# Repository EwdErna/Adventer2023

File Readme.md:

# Blender でキーボードケースのレンダーを作る

これを、  
  
こうします。  

## 目次

星が一つついている項目(★)はキーキャップ関連です。  
星が二つ付いている項目(★★)は基板関連です。  
必要ない場合は飛ばしてかまいません。  
特に、★ を行った場合 ★★ はほぼ見えません。  
見えないところにこだわる~~異常者~~方だけが参照していただければよいかなと思ってます。

- ★ キーボードを作る
  - ★ Keyboard Layout Editor でキー配置を作る
  - ★★ KiCAD で基板データを作る
  - ケースを作る
- Blender 用に出力する
  - ケースの出力
  - ★ キー配置の出力
  - ★★ 基板の出力
- Blender の設定
  - 単位関連の設定
  - レンダリング関連の設定
  - ★ キー配置インポート用の設定
- ケースを配置する
  - インポート
  - 座標設定
  - ★ 面をきれいにする
- マテリアルをいじる
  - アルマイト
  - ヘアライン
  - スモークアクリル
- レンダリング
  - 足場
  - ライティング
  - カメラ
  - レンダリング
- ★ キーキャップを配置する
  - keyboard-layout.json の読み込み
  - サイズ設定
  - 配置
- ★★ 基板を配置する
  - 基板データの読み込み
  - データクリーンアップ
  - 配置

## キーボードを作る

レンダーに使うキーボードの各種データを作成していきます。すでに存在する場合は飛ばしてよいです。

### ★ Keyboard Layout Editor でキー配置を作る

記事冒頭で提示したように、キーボードの配置を考えていきます。  

こちらのサイトで、自分の使いたいキー配置を作成します。  
[Keyboard Layout Editor](http://keyboard-layout-editor.com)  
刻印や色、(一部ですが)プロファイルも反映されるので、こだわる場合は設定しておくとよいです。

詳しい使い方はあちこちのサイトに紹介されているので触れません。

### ★★ KiCAD で基板データを作る

上記の配置を達成する基板データを作成します。  

こちらも詳細は省きます。サリチル酸さんの本を買ってください。 (ダイマ)
https://booth.pm/ja/items/4410329

### ケースを作る

上記のキーボードを収めるケースを作成します。  

特に制約はないですが、自分のデータでは以下のように基板を収める部分(の、bounding box)が原点に対して上下・左右対称になるよう作成しています。  
  
また図にはありませんが、PCB が水平な状態で入る向き(伝わる？)で作るのもおすすめです。  
後々位置合わせが楽になるので意識してみるとよいと思います。

参考文献としてサリチル酸さんの本を買ってください。(ダイマ)  
https://salicylic-acid3.booth.pm/items/4982088

## Blender 用に出力する

作成した各種データを、Blender で読み込める形式で出力します。

### ケースの出力

以下は FreeCAD の場合です。他の CAD を使う方はいい感じに読み替えてください。

パーツを選択した状態で、`ファイル` > `エクスポート`を選択します。  

Blender で読み込める形式ならどれを選んでもよいですが、ここでは`Wavefront OBJ`形式を選択しています。  

Blender で(デフォルトで)読み込める形式は、Blender を開き`File` > `Import`から確認できます。  
  
形式によって扱いずらいデータが出てくる場合もあるので、個人的には OBJ で済ませるのが良いかなと思っています。

### ★ キー配置の出力

KLE にて、以下どちらかの方法で keyboard-layout.json をダウンロードできます(どっちも同じです)。  

### ★★ 基板の出力

以下は KiCAD の場合です。他の EDA を使う方はいい感じに読み替えてください。

`ファイル` > `エクスポート` > `VRML...`を選択します。  
  
VRML を使っている理由としては、

- Blender で直接インポートできる
- 色付き

の二点です。あとでわかる通りめちゃくちゃめんどくさいデータ構造なので、ほかにいいものあれば教えてください。

## Blender の設定

やや個人の好みが入っていますがこの設定しとくとやりやすいよってやつです。

### 単位関連の設定

図の三か所を変更します。  
  
左から順に、

- 単位系のデフォルトを`mm`に
  - キーボードのスケールに合わせる
- カメラのクリッピング距離を変更
  - デフォルトだとちょっと近づくとすぐに見えなくなる
  - 実際の値はよしなに
- グリッドを`mm`単位に
  - デフォルトだと広すぎて扱いづらい(好み)
  - 実際の値はよしなに

### レンダリング関連の設定

好みです。ただし、以下の解説では Cycles を前提にしたマテリアル設定が出てくるため、Eevee では見た目が大きく異なる/使用できない場合があります。  

- `Render Engine`を`Cycles`に
- `Device`を設定
  - Cycles にしない場合は出てこない
  - GPU があるなら GPU Compute に
  - ないなら CPU のままでよいがクソ重い
    - 比較材料として、今回のレンダリング画像の出力には CPU で 3 時間、GPU で 5 分ほどかかりました。

### ★ キー配置インポート用の設定

以下のサイトから Blender のアドオンをダウンロードします。  
  
https://github.com/Kirpal/Keyboard-Layout-Editor-for-Blender/releases/tag/v3.3

ダウンロードした zip を Blender で読み込みます。  

インストールしたアドオンを有効化します。  

## ケースを配置する

ケースデータを読み込み、シーンに配置していきます。

### インポート

`File` > `Import` > `Wavefront(.obj)`を選択します。  
obj 以外で出力した場合は適切に読み替えてください。  

### 座標設定

出力時の設定にもよりますが馬鹿デカいものが出てくると思います。  
その場合はいい感じにサイズを縮小してください。  
画像の場合、`s.001` > `右クリックorEnter`で 1/1000 にすると実際のスケールになります。

原点や向きが扱いづらいのでいい感じにしていきます。  
順に、

- `gz88.888`(数値は CAD 中の原点からケース最下部までの距離)
- `gy88.888`(同様にケース底面までの距離)
- `rx88.888`(同様にケース底面が水平になる角度)

で修正しました。  

### 面をきれいにする

好みです＆とても面倒です。気にならない方はぜひ飛ばしてください。  
個人的にはかなり見た目に影響すると思っているので、できるだけ設定しています。

CAD から読み込んだ OBJ データは下図のように曲面がカクカクに描画されていることがほとんどです。  
  
これを、以下のように滑らかにします。  

#### デフォルト設定でいい感じになるか試す

「滑らかな曲面」と「角ばった辺」で、大きく角度が異なる場合はこの設定のみで事足ります。  
オブジェクトを選択した状態で、`Object` > `Shade Auto Smooth` を選択します。  

「滑らかな曲面」と判定される角度を調節することで、きれいに曲面とエッジが分かれてくれる場合はこれで終了です。  

#### いい感じにならない場合

今回の自分のケースのように、角度の浅い面のつながりがある場合、Auto Smooth だけでは対応しきれません。  

その場合は、「角度が浅いが角の出る辺」をそのようにマークしてあげることで、いい感じになります。

平らな面の一つを選択し、`Select` > `Select Linked` > `Linked Flat Faces`を選択します。  
  
この時画面左下にメニューが出ていますので、調整します。小さく設定することで浅い角度の面でも切り分けてくれるようになりますが、フィレットのような浅い角度でつながっている曲面もぶつ切りになるようになります。  
  
滑らかにつながっていてほしい面はできるだけつながっていて、つながっていてほしくない＝エッジがはっきり出てほしい面は一つもつながっていない状態にします。(後者は後から分けるのが面倒です。前者を妥協して後から直すほうが楽)  
`Select` > `Select Loops` > `Select Boundary Loop`を選択することで、選択された面の外周の辺だけを選択できます。  
  
この状態で、`Ctrl+E` > `Mark Sharp`を選択することで辺を「角の出る辺」としてマークすることができます。  

この操作を繰り返すことで、いい感じにエッジが出るように設定できます。  

## マテリアルをいじる

せっかくレンダリングするのでマテリアルをいい感じにしましょう。  
細かい設定だったり一般論だったりは他のサイトに任せますので、よく使ってるマテリアル設定を貼ります。  
※前述したとおり Cycles 前提のマテリアルです。あと適当なのでそんなにそれっぽくなかったりクソ重かったりします。

### アルマイト

### ヘアライン

### スモークアクリル

## レンダリング

レンダリングに向けて準備をし、実際にレンダリングしていきます。

### 足場

適当です。  
`Add` > `Mesh` > `Cube`を追加し、`s` > `Shift+z` > `2000`で 2m 四方の大きさにしたものを位置調節しました。  
  
マテリアルも適当です。なんか木っぽい感じにしようとしました。  

### ライティング

`Add` > `Light` > `Area Light`からライトを追加します。他のでもいいです。  
三点照明法っぽい感じにしようとしてます。毎度むずいです。誰か助けてくれ  
  
見切れてますが上のほうに一個ライトがあります。

### カメラ

`Add` > `Camera`からカメラを追加します。なんかいい感じに見えるように配置します。誰か助けてくれ  

### レンダリング

`Image` > `Render Image`を押すとレンダリングが始まります。GPU がない人は耐えましょう。  

一旦完成です。  
ここから先はこだわる人向けです。

## ★ キーキャップを配置する

キーボードなのでキーキャップぐらいほしいですよね。  
安心してください、簡単にできますよ。

### keyboard-layout.json の読み込み

最初のほうでダウンロードした json ファイルを Import します。

`File` > `Import` > `KLE Raw Data(.json)`があるので、こちらを選択します。  

ダウンロードした json ファイルを開きます。  

ちょっと時間がかかりますがインポートが始まります。

### サイズ設定

いつも通りでかいのでサイズ調整します。(オレンジのやつがケース)  

選択が外れてしまっている場合、Keyboard というコレクションが追加されているので`右クリック` > `Select Objects`ですべてのパーツを選択できます。  

今回は`s.1`で 1/10 にしました。  

雑なケースがついてきますがいらないので消します。  

スイッチもついてます。なぜかちょっと小さいのでそのまま使うのはお勧めしません。  
使う場合はすべて選択したのち、pivot を Individual Origin にしたうえで、`s1.27`とすると実寸大に近くなります。  

私は後述の設定をしているので基本消してます。

さすがに時間がかかるので今回はやりませんでしたが、普段はさらに、キーキャップのポリゴン数を減らすクリーンアップ作業をしています。

### 配置

配置を楽にするため、すべてのオブジェクトを一つのオブジェクトの子にします。

`Add` > `Empty` > `Plain Axis`から空オブジェクトを作成します。  
  
変なことをしてなければキーキャップ外形の中心に十字架の中心がいるはずです。ずれていたらインポートからやり直したほうが早いです。

キャップ(スイッチを残している人はスイッチも)をすべて選択した後、先ほどの empty を追加選択します(十字架が薄いオレンジ、ほかが濃いオレンジになると思います。色変えてる人は知りません)。  
`Ctrl+p` > `Object`で親子関係を作成します。  
  
親子関係を作ったので、empty を移動させたり回転させればキャップがまとめて移動したり回転したりします。

empty をいい感じにケースの床に移動させます。(ずれてないように見えててもやっといたほうが無難です)  
ケースを選択した状態で、`Object` > `Snap` > `Cursor to Selected`を選択します。カーソル(赤白の点線の丸と黒いひげのやつ)がケース原点に移動します。

Empty を選択した状態で、`Object` > `Snap` > `Selection to Cursor`を選択します。empty 原点がカーソル＝ケース原点に移動します。

あとは、向きや高さを合わせます。先に向きを合わせ(`rx7`：グローバルの x 軸で回転)、その後高さを合わせる(`gzz12`：ローカルの z 軸で移動)と楽です。  

これで完成です。  

ここから先は見えないところに時間をかけてこだわる~~狂人~~僕みたいな人向けの内容になります。

## ★★ 基板を配置する

基板のデータを読み込み、キーキャップの下に仕込みます。  
プレート等も同様の手順で作成できるので応用してみてください(svg あるならそっちのほうが楽です)。

### 基板データの読み込み

先にコレクションを作り、選択しておくと楽です。(キーキャップの項で説明した Select Objects がほぼ必須)  
`File`>`Import`>`X3D Extensible 3D(.x3d/.wrl)`から KiCAD が吐いた wrl ファイルを読み込みます。  

### データクリーンアップ

毎度のことながらクソでかいので縮めます。 ... の前に、まずはデータをまとめます。  
Hierarcy を見るとわかる通り非常にオブジェクトが多いです。何かというと、キースイッチの各面がなぜかバラバラに出てきています。(SHAPE_1 ～ SHAPE_160 くらいまでがキースイッチのポリゴン)  
そのままでは扱えたものではないので、一つのオブジェクトにまとめてしまいます。

hierarchy を一番下までスクロールし(この時選択解除しないように気を付けてください)、下から何個目かにある、マテリアルが緑色のオブジェクトを`Ctrl+Click`で選択してください。  
基板の面面か裏面で、原点が基板中央になっています(なっていなかったら、そうなっている別のオブジェクトを使ってください)。  

`Ctrl+j`で一つのオブジェクトにまとめ、その後 pivot を Cursor にした状態で縮小(`s.001`)します。

まとめただけで面がばらばらだとライティング時に不都合なので、くっつけられる場所はくっつけていきます。  
編集モードに入り、選択を全解除します。その後、以下の手順をすべてのマテリアルに対して繰り返します。  

- マテリアルを一つ選択し、`Select`で対応する面を選択します。
- `Mesh` > `Clean Up`(u キー) >`Merge by distance`(b キー)を選択します。
- (初回のみ)Merge Distance を 0.01mm とかそこらにします(細かい部品がつぶれるのを防ぐため。よしなに)。
- 何もないところをクリックし、選択解除します。

すべてのマテリアルについてマージしたらクリーンアップ完了です。

キーキャップ同様今回はスキップしましたが、普段は各部品の Smooth 設定をやってます。バカじゃないの？

### 配置

オブジェクトモードに戻り、キーキャップの時と同様`Object`>`snap`を活用して原点に位置合わせします。  

回転、座標合わせをして完成です。  

最終的なレンダリング結果はこちら。

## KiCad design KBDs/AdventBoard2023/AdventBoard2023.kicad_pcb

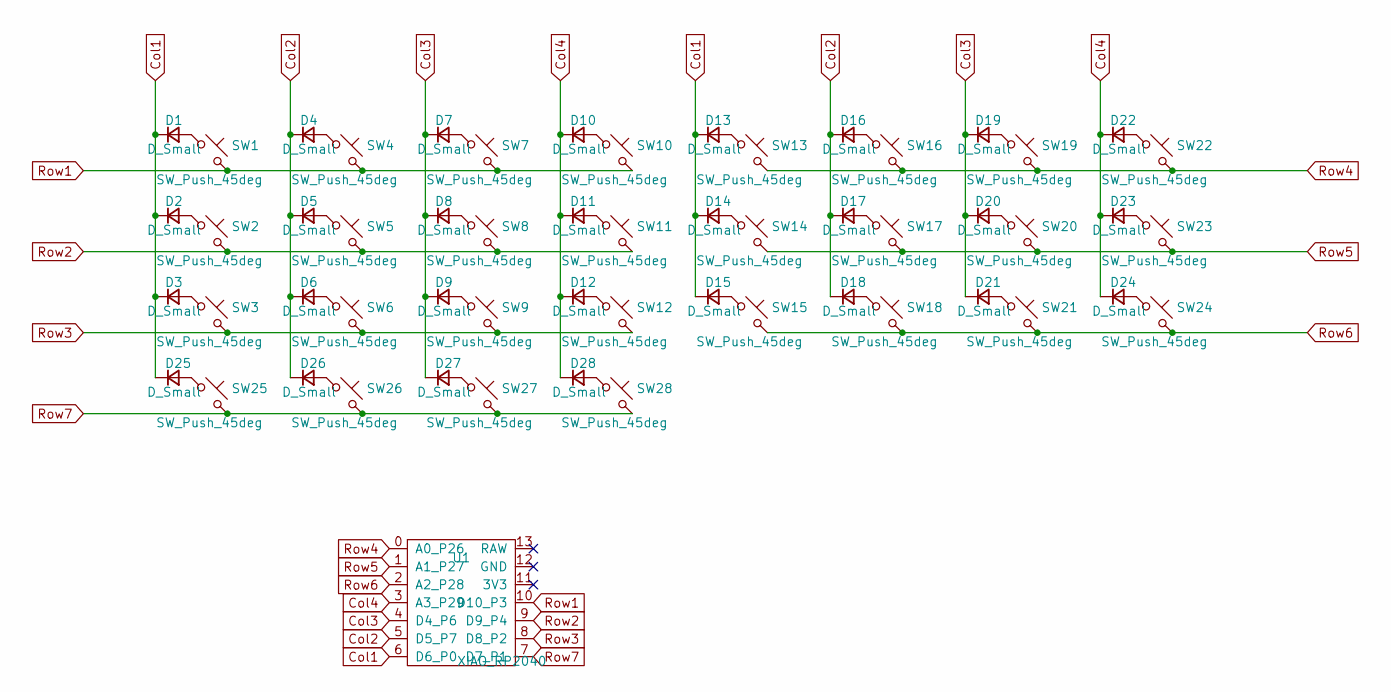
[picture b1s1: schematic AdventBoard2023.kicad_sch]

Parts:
D1, D2, D3, D4, D5, D6, D7, D8, D9, D10, D11, D12, D13, D14, D15, D16, D17, D18, D19, D20, D21, D22, D23, D24, D25, D26, D27, D28: D_Small; D3_SMD
SW1, SW4, SW5, SW6, SW7, SW8, SW9, SW10, SW11, SW12, SW13, SW14, SW15, SW16, SW17, SW18, SW19, SW20, SW21, SW22, SW28: SW_Push_45deg; SW_Cherry_MX1A_1.00u_PCB
SW2, SW23, SW26, SW27: SW_Push_45deg; SW_Cherry_MX1A_1.50u_PCB
SW3, SW25: SW_Push_45deg; SW_Cherry_MX1A_1.25u_PCB
SW24: SW_Push_45deg; SW_Cherry_MX1A_1.75u_PCB
U1: XIAO_RP2040; MOUDLE14P-SMD-2.54-21X17.8MM

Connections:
Col1: D1.1 (K), D2.1 (K), D3.1 (K), D13.1 (K), D14.1 (K), D15.1 (K), D25.1 (K), U1.6 (D6_P0)
Col2: D4.1 (K), D5.1 (K), D6.1 (K), D16.1 (K), D17.1 (K), D18.1 (K), D26.1 (K), U1.5 (D5_P7)
Col3: D7.1 (K), D8.1 (K), D9.1 (K), D19.1 (K), D20.1 (K), D21.1 (K), D27.1 (K), U1.4 (D4_P6)
Col4: D10.1 (K), D11.1 (K), D12.1 (K), D22.1 (K), D23.1 (K), D24.1 (K), D28.1 (K), U1.3 (A3_P29)
unnamed: D1.2 (A), SW1.1
unnamed: D2.2 (A), SW2.1
unnamed: D3.2 (A), SW3.1
unnamed: D4.2 (A), SW4.1
unnamed: D5.2 (A), SW5.1
unnamed: D6.2 (A), SW6.1
unnamed: D7.2 (A), SW7.1
unnamed: D8.2 (A), SW8.1
unnamed: D9.2 (A), SW9.1
unnamed: D10.2 (A), SW10.1
unnamed: D11.2 (A), SW11.1
unnamed: D12.2 (A), SW12.1
unnamed: D13.2 (A), SW13.1
unnamed: D14.2 (A), SW14.1
unnamed: D15.2 (A), SW15.1
unnamed: D16.2 (A), SW16.1
unnamed: D17.2 (A), SW17.1
unnamed: D18.2 (A), SW18.1
unnamed: D19.2 (A), SW19.1
unnamed: D20.2 (A), SW20.1
unnamed: D21.2 (A), SW21.1
unnamed: D22.2 (A), SW22.1
unnamed: D23.2 (A), SW23.1
unnamed: D24.2 (A), SW24.1
unnamed: D25.2 (A), SW25.1
unnamed: D26.2 (A), SW26.1
unnamed: D27.2 (A), SW27.1
unnamed: D28.2 (A), SW28.1
Row1: SW1.2, SW4.2, SW7.2, SW10.2, U1.10 (D10_P3)
Row2: SW2.2, SW5.2, SW8.2, SW11.2, U1.9 (D9_P4)
Row3: SW3.2, SW6.2, SW9.2, SW12.2, U1.8 (D8_P2)
Row4: SW13.2, SW16.2, SW19.2, SW22.2, U1.0 (A0_P26)
Row5: SW14.2, SW17.2, SW20.2, SW23.2, U1.1 (A1_P27)
Row6: SW15.2, SW18.2, SW21.2, SW24.2, U1.2 (A2_P28)
Row7: SW25.2, SW26.2, SW27.2, SW28.2, U1.7 (D7_P1)

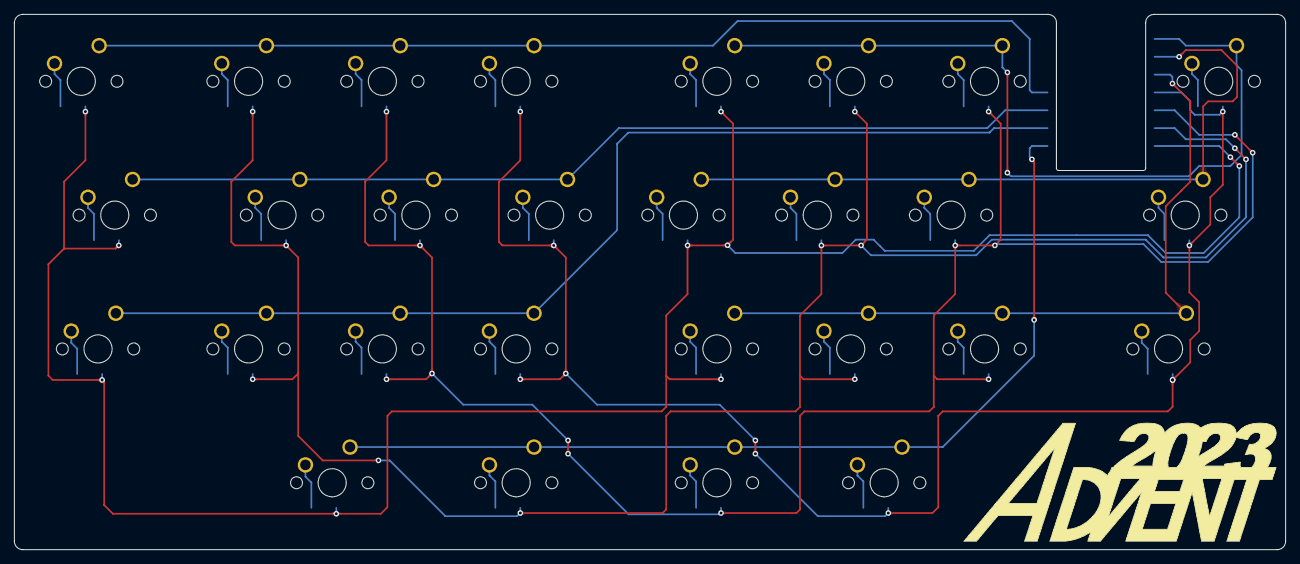
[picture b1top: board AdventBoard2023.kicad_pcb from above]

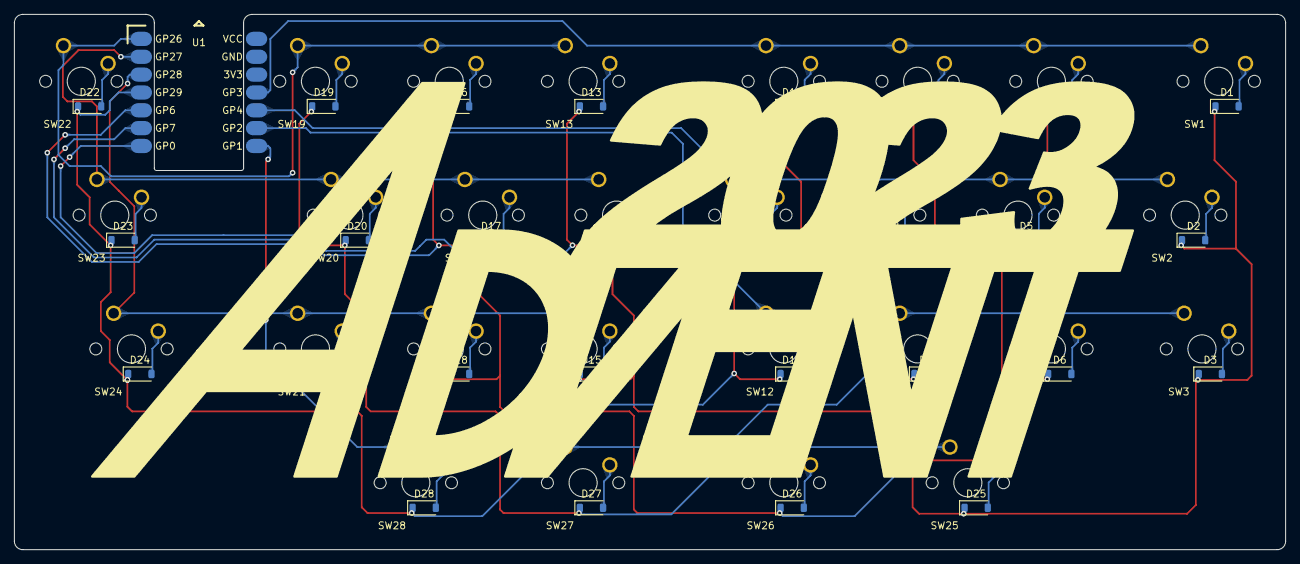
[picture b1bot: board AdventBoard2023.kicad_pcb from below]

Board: 2 copper layers, 181.0 x 76.2 mm, 57 parts (29 on the bottom side), 39 nets.

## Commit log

2023-12-03 finished work and screenshots
2023-12-03 write up doc ( some lacking images)
2023-12-04 add gitignore (too late)
2023-12-16 finished
